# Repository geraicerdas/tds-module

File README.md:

### Repository Content
* **/firmware** : Arduino example codes (.ino)
* **/hardware** : Schematic files (.pdf) some of older version included Eagle design files (.sch and .brd)
* **/production** : gerber file for pcb manufacturing

You can purchase this product from  

# TDS Module

TDS (Total Dissolved Solids) indicates how many milligrams of soluble solids are dissolved in one liter of water. In general, the higher the TDS value, the more soluble solids are dissolved in water. This module can be used in DIY water quality application, such as domestic water analysis and hydroponics. The latest version already have temperature compensation for better accuracy.

## How To Use
For the hardware you will need :
- Arduino or other compatible microcontroller
- TDS module with TDS probe and waterproof DS18B20
- Jumper wires

(optional : if you want to use Arduino Library) In the Arduino IDE, make sure :
- you have installed Library : [GravityTDS](https://github.com/DFRobot/GravityTDS) by DFRobot (This library tested on Arduino UNO, and will not work with Arduino Leonardo, ESP32)

Connect the TDS module to the MCU
| Arduino / Other MCU | TDS Module |
| ------------- |:-------------|
| 5V / 3.3V | VCC |
| Analog Input Pin | TDS |
| Digital Input Pin | TEM |
| GND | GND |

Upload the code in the firmware folder, and you will get the temperature and compensated TDS value of the water on the Serial Monitor

## Notice
- The probe can not to be used in water above 55 degrees centigrade.
- The probe can not be too close to the edge of the container, otherwise it will affect the reading

## Development logs
V3.0
- Add 3P PH2.0 connector for waterproof temperature sensor DS18B20
- Change 3P terminal to 4P terminal for additional temperature output pin

V2.1
- Rearrange component placement for better layout, fixing wrong decoupling capacitor position
- Change PCB color

V2.0
- Change PCB shape

V1.0
- Initial design

## PCB and Parts

If you want to make your self, just download the gerber file in production folder. Send it to your fav pcb manufacturer. And dont forget to get the Bill of materials :
|Qty | Part Name | Parts | MPN |
| ------------- |:-------------|:-------------| -----:|
|9|Capacitor 0603 100nF|C1, C2, C6, C7, C9, C11, C13, C16, C18|
|3|Capacitor 0603 10uF|C8, C10, C12|
|1|Capacitor 0603 1nF|C15|
|2|Capacitor 0603 1uF|C14, C17|
|2|Capacitor 0603 4.7uF|C4, C5|
|1|Capacitor 3216 100uF|C3|
|2|Resistor 0603 100K-1%|R4, R10|
|7|Resistor 0603 10K-1%|R5, R6, R7, R8, R9, R11, R12|
|1|Resistor 0603 1M-1%|R1|
|1|Resistor 0603 4K7-1%|R14|
|1|Resistor 0603 5.6K-1%|R2, R13|
|1|Resistor 0603 6.8K-1%|R3|
|5|Diode SOD-323 1N4148|D1, D2, D3, D4, D5|
|1|SMD LED 0805|L1|
|1|LMV324 SO-14|U1|
|1|TPS60400 SOT-23-5|U2|
|1|CD4060-BM SO-16|U3|
|1|XC6206P302MR SOT-23|U4|
|1|XH2.5 2P SMD connector|J3|
|1|PH2.0 3P SMD connector|J5|
|1|Teminal Connector 4P 5.08|J6|

Below is the previous version of our TDS Module. We keep this for your references.

### Version 2.1

### Version 1.0

## License
*We invests time and resources providing this open-source hardware, please support us by purchasing our products.*

*Designed by **[Insan Sains](https://www.youtube.com/insansains)** for **[Gerai Cerdas](https://geraicerdas.com)**, with contributions from the open source community. Creative Commons Attribution/Share-Alike, all text above must be included in any redistribution. See license.txt for additional information.*

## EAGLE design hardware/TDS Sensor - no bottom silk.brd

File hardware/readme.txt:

For some reason the schematic with bottom silkscreen is larger than allowable github file size,
so the bottom silkscreen removed to reduce it size.

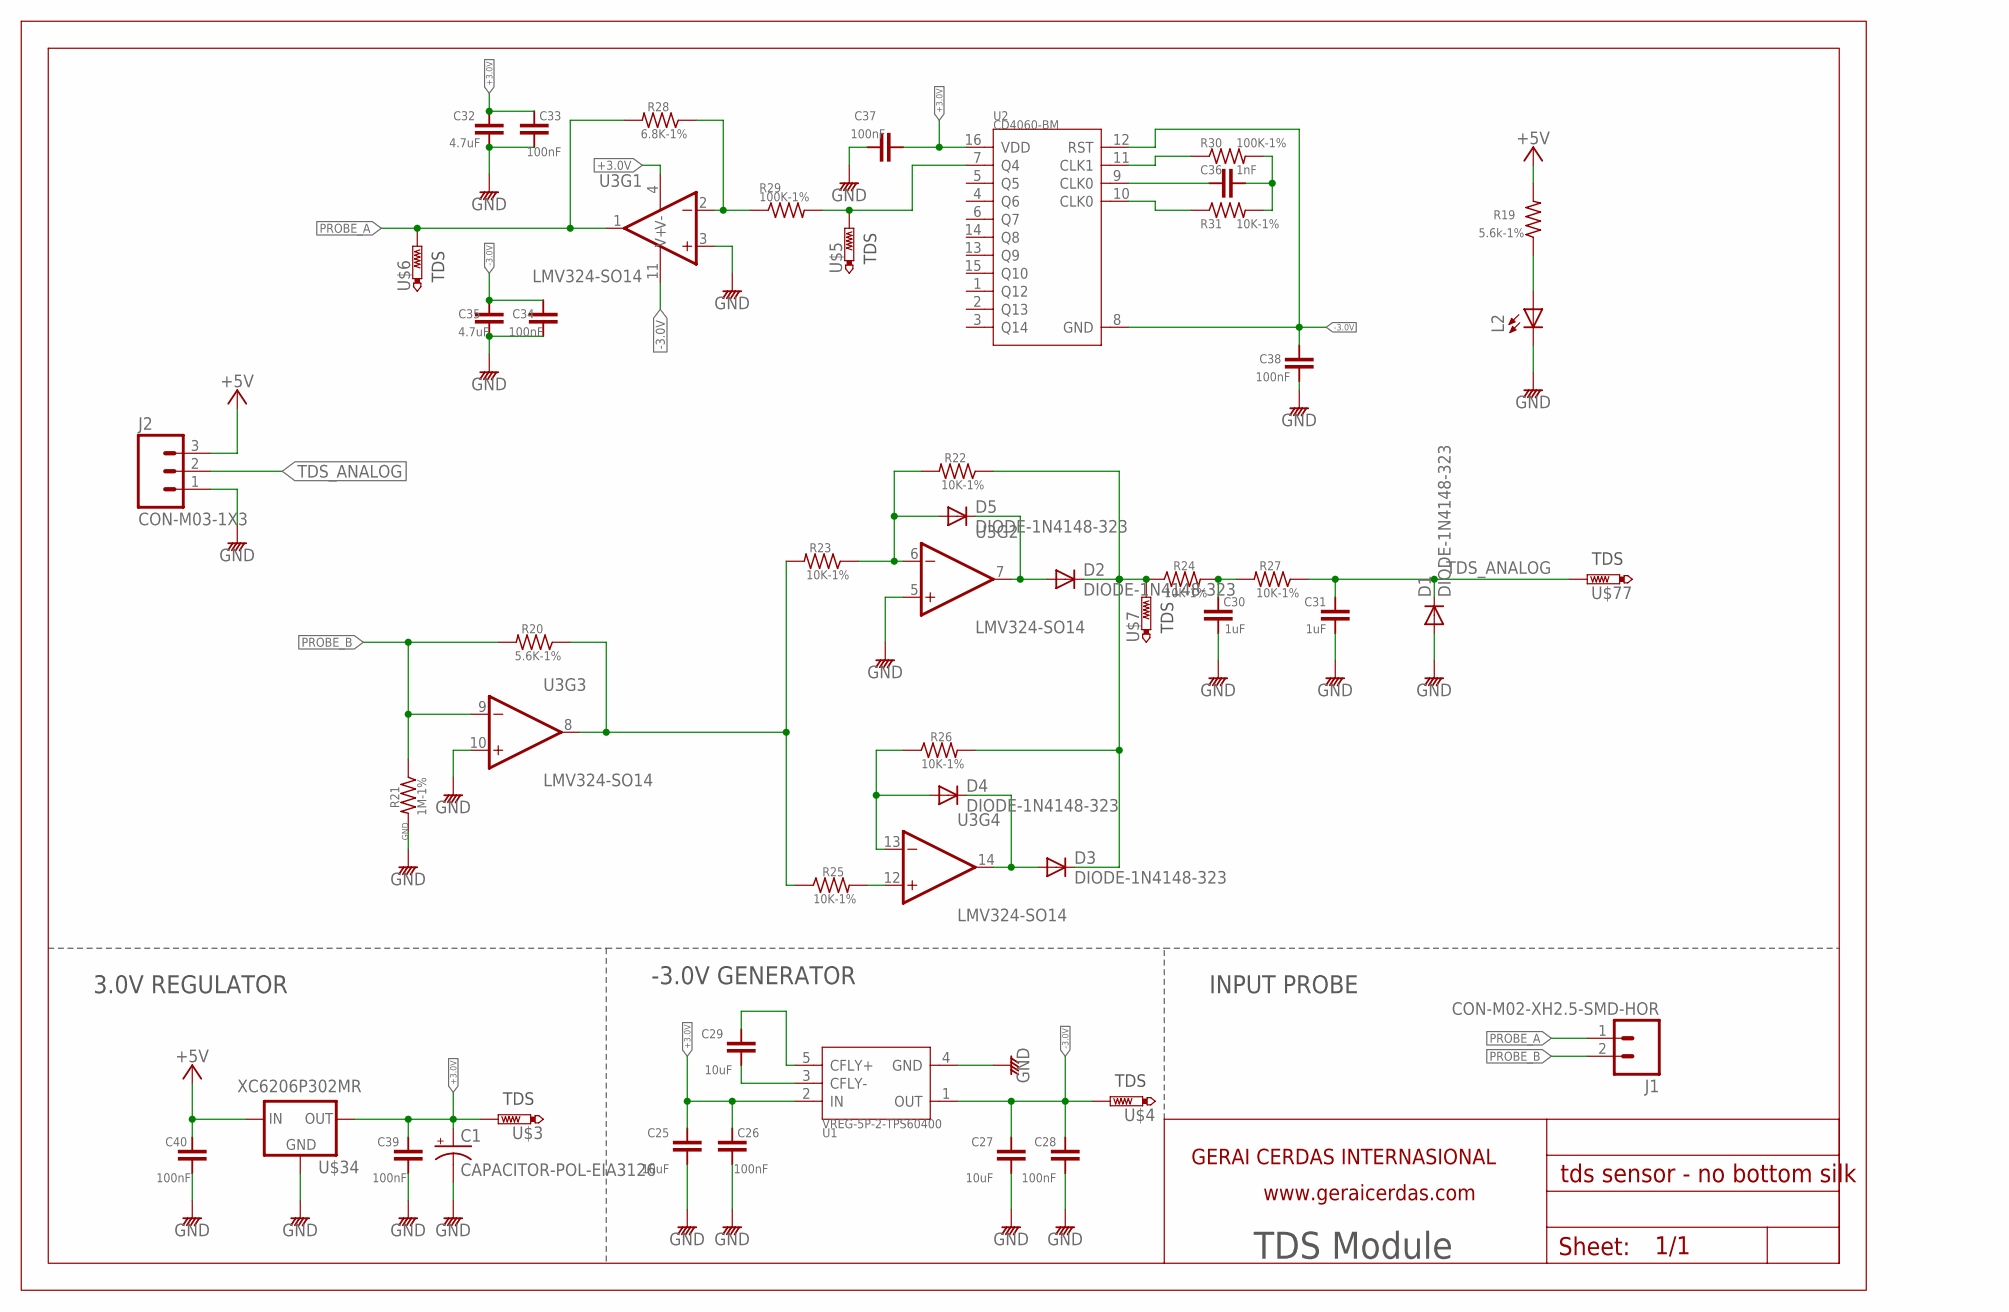
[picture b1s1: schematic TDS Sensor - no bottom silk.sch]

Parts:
C1: CAPACITOR-POL-EIA3126; EIA3126
C25, C27, C29: 10uF; C0603
C26, C28, C33, C34, C37, C38, C39, C40: 100nF; C0603
C30, C31: 1uF; C0603
C32, C35: 4.7uF; C0603
C36: 1nF; C0603
D1, D2, D3, D4, D5: DIODE-1N4148-323; SOD-323
J1: CON-M02-XH2.5-SMD-HOR; JST-XH2.5-2P-SMD-HORZ
J2: CON-M03-1X3; CON-M03X1
L2: LED-SMD0805; LED0805
R19: 5.6k-1%; R0603
R20: 5.6K-1%; R0603
R21: 1M-1%; R0603
R22, R23, R24, R25, R26, R27, R31: 10K-1%; R0603
R28: 6.8K-1%; R0603
R29, R30: 100K-1%; R0603
U1: VREG-5P-2-TPS60400; SOT-23-5
U2: CD4060-BM; SO-16
U3: LMV324-SO14; SO-14
U$3, U$4, U$5, U$6, U$7, U$77: TDS; TESTPAD_2.54
U$28: FRAME; A4-HOR
U$34: XC6206P302MR; SOT-23

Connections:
+3.0V: C1.A (+), C25.2, C26.2, C32.2, C33.2, C37.1, C39.2, U1.2 (IN), U2.16 (VDD), U3.4 (V+), U$3.TP, U$34.2 (OUT)
+5V: C40.2, J2.3, R19.2, U$34.3 (IN)
-3.0V: C27.2, C28.2, C34.2, C35.2, C38.2, U1.1 (OUT), U2.8 (GND), U2.12 (RST), U3.11 (V-), U$4.TP
GND: C1.C (-), C25.1, C26.1, C27.1, C28.1, C30.1, C31.1, C32.1, C33.1, C34.1, C35.1, C37.2, C38.1, C39.1, C40.1, D1.A, J2.1, L2.C, R21.2, U1.4 (GND), U3.3 (+IN), U3.5 (+IN), U3.10 (+IN), U$34.1 (ADJ)
unnamed: R25.2, U3.12 (+IN)
unnamed: L2.A, R19.1
unnamed: D5.A, R22.2, R23.1, U3.6 (-IN)
unnamed: D2.A, D5.C, U3.7 (OUT)
unnamed: D2.C, D3.C, R22.1, R24.1, R26.2, U$7.TP
unnamed: D4.A, R26.1, U3.13 (-IN)
unnamed: D3.A, D4.C, U3.14 (OUT)
unnamed: R20.1, R23.2, R25.1, U3.8 (OUT)
unnamed: C30.2, R24.2, R27.2
unnamed: R28.1, R29.1, U3.2 (-IN)
unnamed: C29.2, U1.5 (CFLY+)
unnamed: R30.1, U2.11 (CLK1)
unnamed: C36.1, U2.9 (CLK0)
unnamed: R31.1, U2.10 (CLK0)
unnamed: C36.2, R30.2, R31.2
unnamed: R29.2, U2.7 (Q4), U$5.TP
unnamed: C29.1, U1.3 (CFLY-)
PROBE_A: J1.1, R28.2, U3.1 (OUT), U$6.TP
PROBE_B: J1.2, R20.2, R21.1, U3.9 (-IN)
TDS_ANALOG: C31.2, D1.C, J2.2, R27.1, U$77.TP

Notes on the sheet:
TDS Module
INPUT PROBE
3.0V REGULATOR
-3.0V GENERATOR

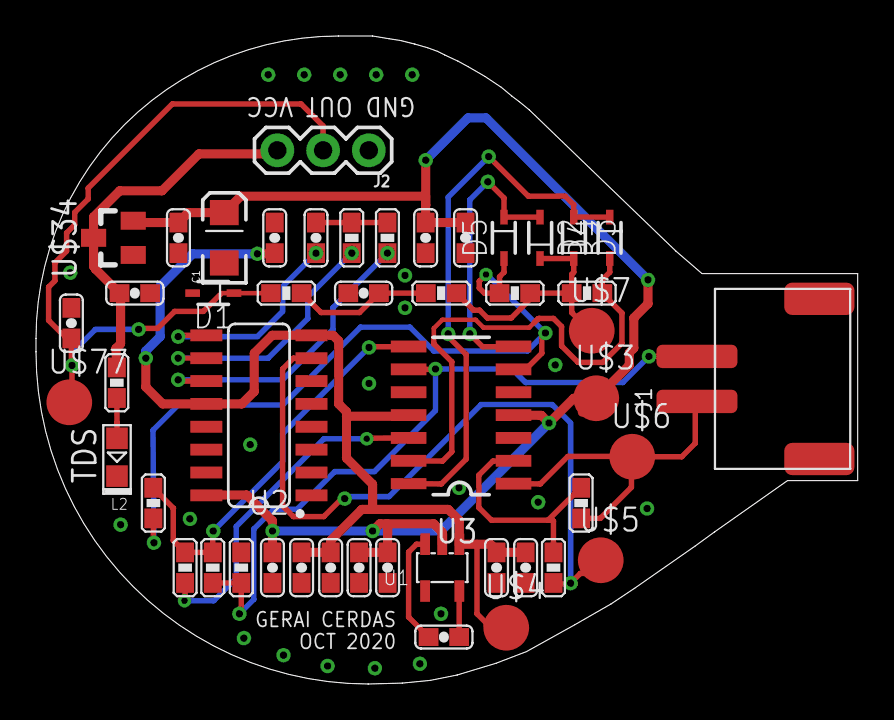
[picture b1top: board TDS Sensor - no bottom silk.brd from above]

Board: 2 copper layers, 45.6 x 36.0 mm, 49 parts (0 on the bottom side), 24 nets.

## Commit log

2020-11-28 Rename GC_TDS_Example.ino to GC_TDS_Example_With_Temp_Compensation.ino
2022-03-06 Rename codes/readme.txt to firmware/readme.txt
2022-03-06 Rename codes/GC_TDS_Example.ino to firmware/GC_TDS_Example.ino
2022-03-06 Rename codes/GC_TDS_Example_With_Temp_Compensation.ino to firmware/GC_TDS_Example_With_Temp_Compensation.ino
